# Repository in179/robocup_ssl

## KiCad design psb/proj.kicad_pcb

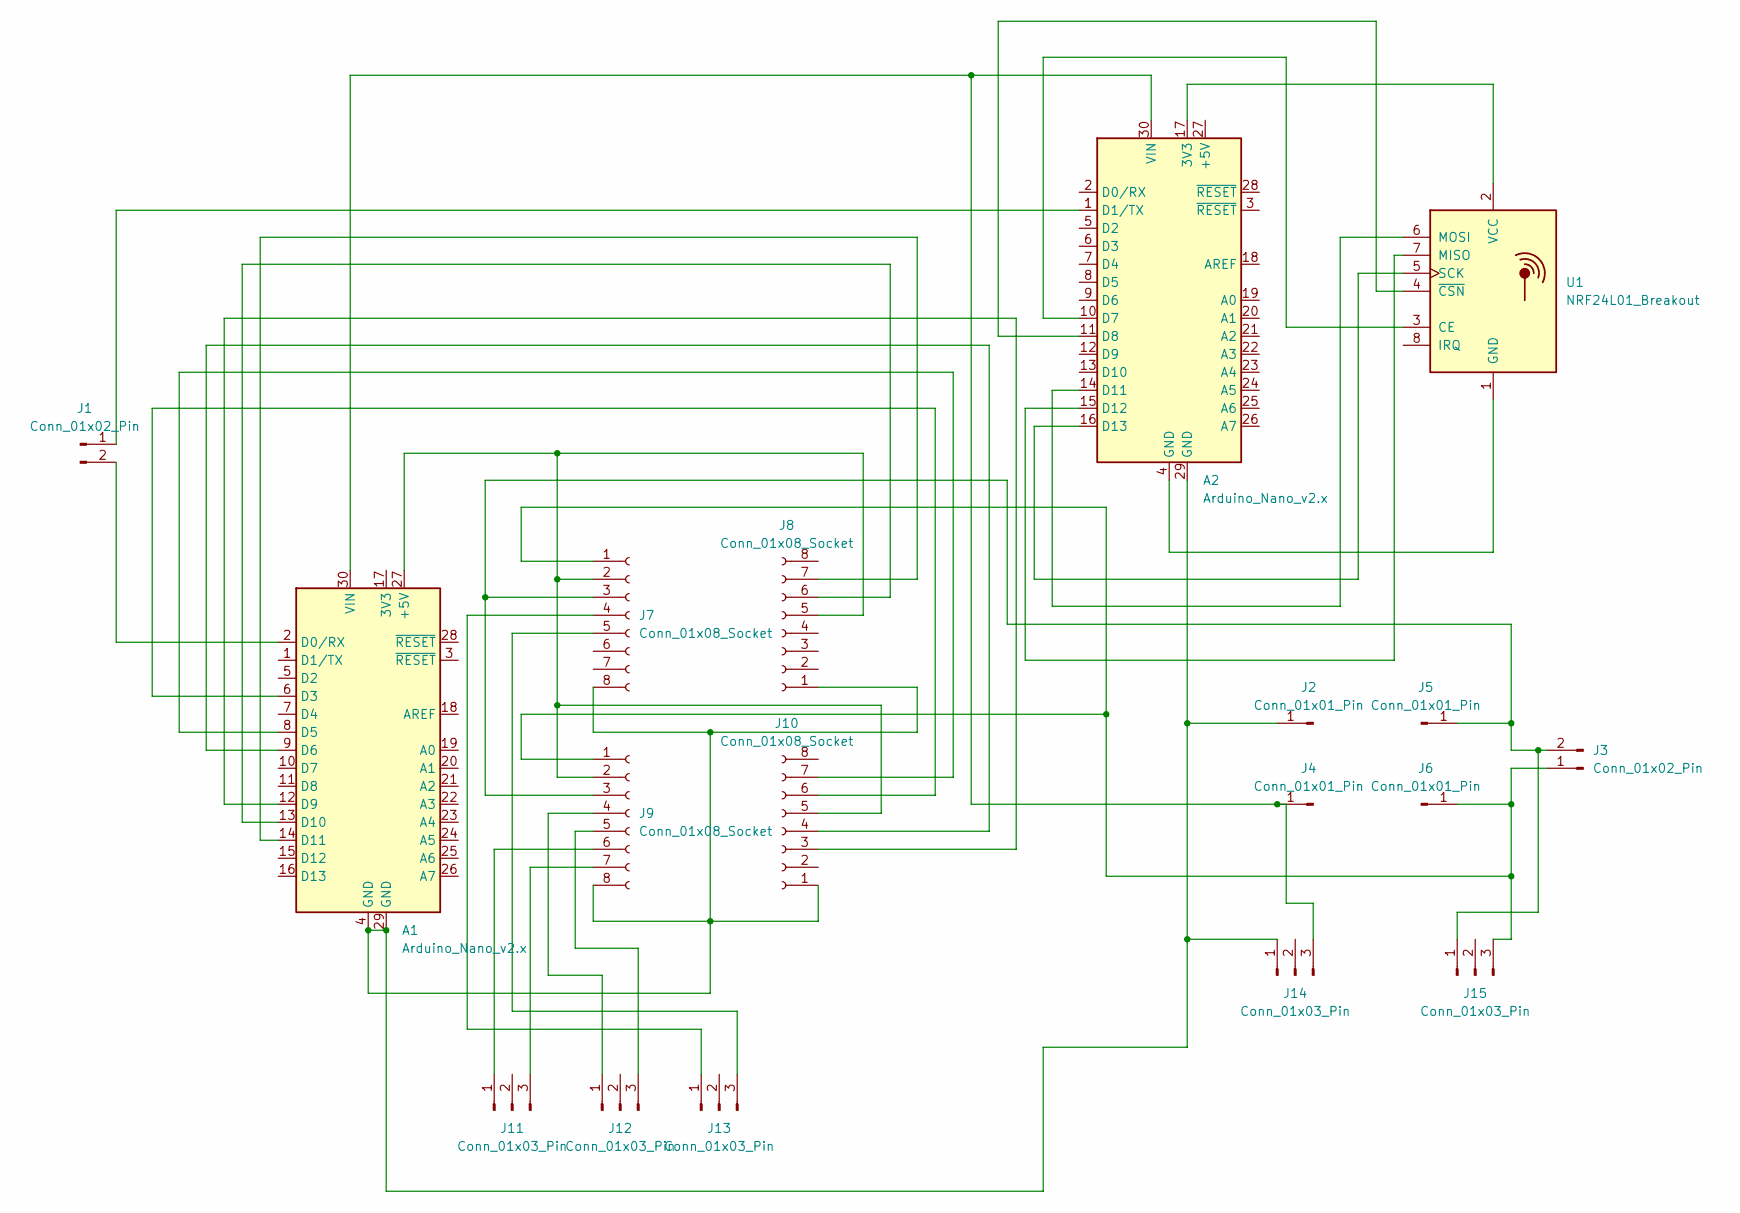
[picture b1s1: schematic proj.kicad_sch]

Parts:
A1, A2: Arduino_Nano_v2.x; Arduino_Nano
J1: Conn_01x02_Pin; PinHeader_1x02_P2.54mm_Vertical
J2, J4, J5, J6: Conn_01x01_Pin; PinHeader_1x01_P1.00mm_Vertical
J3: Conn_01x02_Pin; AMASS_XT60PW-M_1x02_P7.20mm_Horizontal
J7, J8, J9, J10: Conn_01x08_Socket; PinSocket_1x08_P2.54mm_Vertical
J11, J12, J13, J14, J15: Conn_01x03_Pin; PinHeader_1x03_P2.54mm_Vertical
U1: NRF24L01_Breakout; nRF24L01_Breakout

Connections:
unnamed: A1.27 (+5V), J7.2, J8.5, J9.2, J10.5
unnamed: A1.2 (D0/RX), J1.2
unnamed: A1.6 (D3), J10.6
unnamed: A1.8 (D5), J10.7
unnamed: A1.9 (D6), J10.4
unnamed: A1.12 (D9), J10.3
unnamed: A1.13 (D10), J8.6
unnamed: A1.14 (D11), J8.7
unnamed: A1.30 (VIN), A2.30 (VIN), J4.1, J14.3
unnamed: A2.17 (3V3), U1.2 (VCC)
unnamed: A2.1 (D1/TX), J1.1
unnamed: A2.10 (D7), U1.3 (CE)
unnamed: A2.11 (D8), U1.4 (~CSN)
unnamed: A2.14 (D11), U1.6 (MOSI)
unnamed: A2.15 (D12), U1.7 (MISO)
unnamed: A2.16 (D13), U1.5 (SCK)
unnamed: A1.4 (GND), A1.29 (GND), A2.29 (GND), J2.1, J7.8, J8.1, J9.8, J10.1, J14.1
unnamed: J9.6, J11.1
unnamed: J9.7, J11.3
unnamed: J9.4, J12.1
unnamed: J9.5, J12.3
unnamed: J7.4, J13.1
unnamed: J7.5, J13.3
unnamed: J3.2, J5.1, J7.3, J9.3, J15.1
unnamed: J3.1, J6.1, J7.1, J9.1, J15.3
unnamed: A2.4 (GND), U1.1 (GND)

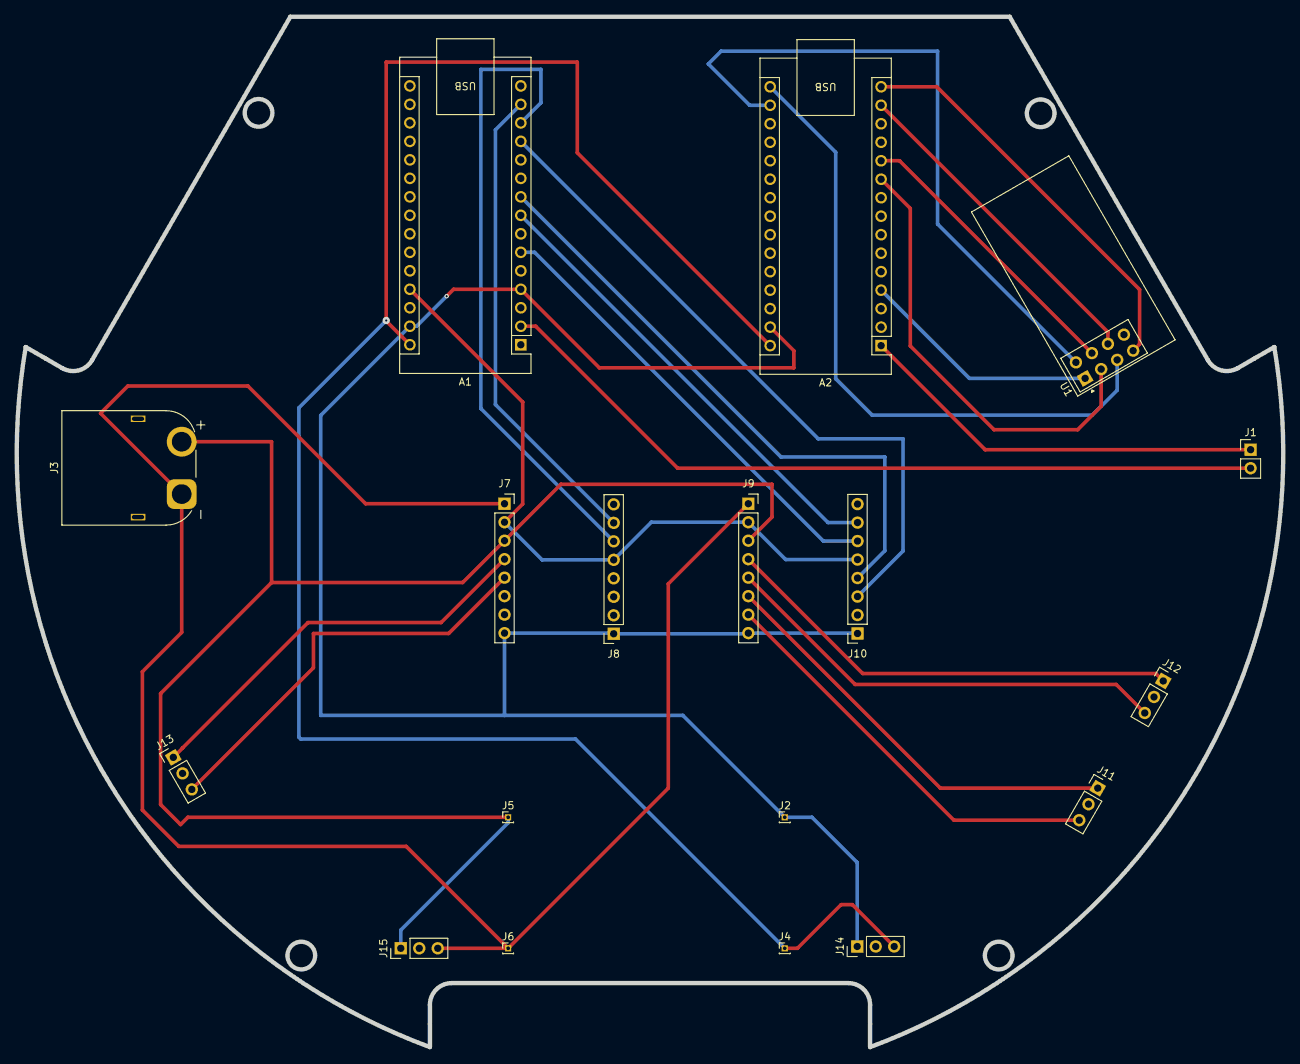
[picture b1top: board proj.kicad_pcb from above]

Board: 2 copper layers, 174.0 x 141.6 mm, 18 parts (0 on the bottom side), 26 nets.
